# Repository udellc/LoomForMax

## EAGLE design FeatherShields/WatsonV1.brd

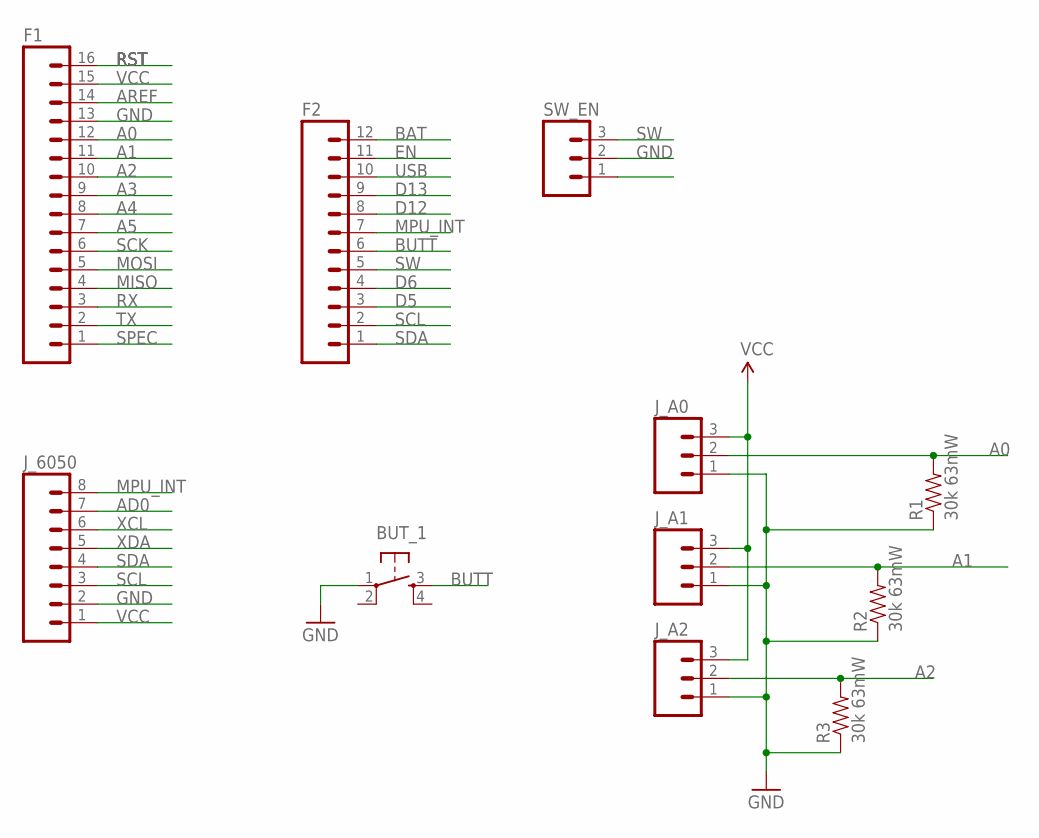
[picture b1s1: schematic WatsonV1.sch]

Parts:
BUT_1: TAC_SWITCHPTH; TACTILE-PTH
F1: M16PTH; 1X16
F2: M12PTH; 1X12
J_6050: M08; 1X08_ROUND
J_A0, J_A1, J_A2: M03JST-PTH-VERT; JST-3-PTH-VERT
R1, R2, R3: 30k 63mW; 1206
SW_EN: M03PTH; 1X03

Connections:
A0: F1.12, J_A0.2, R1.2
A1: F1.11, J_A1.2, R2.2
A2: F1.10, J_A2.2, R3.2
A3: F1.9
A4: F1.8
A5: F1.7
AD0: J_6050.7
AREF: F1.14
BAT: F2.12
BUTT: BUT_1.3, F2.6
D5: F2.3
D6: F2.4
D12: F2.8
D13: F2.9
EN: F2.11
GND: BUT_1.1, F1.13, J_6050.2, J_A0.1, J_A1.1, J_A2.1, R1.1, R2.1, R3.1, SW_EN.2
MISO: F1.4
MOSI: F1.5
MPU_INT: F2.7, J_6050.8
RST: F1.16
RX: F1.3
SCK: F1.6
SCL: F2.2, J_6050.3
SDA: F2.1, J_6050.4
SPEC: F1.1
SW: F2.5, SW_EN.3
TX: F1.2
USB: F2.10
VCC: F1.15, J_6050.1, J_A0.3, J_A1.3, J_A2.3
XCL: J_6050.6
XDA: J_6050.5

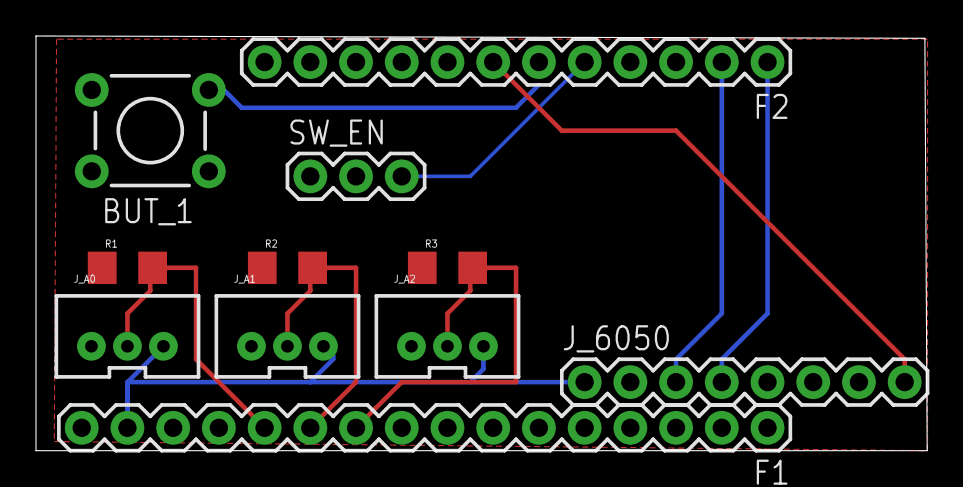
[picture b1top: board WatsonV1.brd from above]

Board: 2 copper layers, 49.5 x 23.0 mm, 11 parts (0 on the bottom side), 10 nets.

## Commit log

2020-06-19 Push to Max1
    LoomForMax push to master V1, actuator dispatching needs fixing. Fixed broadcast IP for Max packets
2020-07-30 Upload Max8 Abstractions
2020-07-31 fix musiclinks udpreceive bug
2020-07-31 Fix clock sync issues
2020-08-06 Updates aug 6 musiclinks chords
2020-08-06 chordDeg fix
2020-08-06 fix musiclinks all update
2020-08-26 LoomFixes
2020-08-27 FixOptron
2020-08-27 optronUpdate
2020-09-15 Update all
2020-09-22 WatsonPCB
2020-10-25 Remove .DS_Store from repo, add .DS_Store to gitignore
2020-10-25 Switch library name to 'LoomForMax' to avoid conflicts with regular Loom
2020-10-25 Add APWiFi module skeleton
2020-10-29 Reorganization within module hierarchy - compiles, needs cleanup
2020-11-02 AP mode generally still works, not sure what's up with occasional unreliability
2020-11-02 Remove remnant debugging print
2020-11-07 Switching to client mode works
2020-11-07 Cleanup
2020-11-07 Switching from client mode works
2020-11-07 Comment fix
2020-11-07 Remove .DS_Store files
2020-11-07 Add example
2020-12-01 upload ICST

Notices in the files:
parts and their libraries:
SparkFun-Retired: Licensing:Creative Commons ShareAlike 4.0 International - https://creativecommons.org/licenses/by-sa/4.0
